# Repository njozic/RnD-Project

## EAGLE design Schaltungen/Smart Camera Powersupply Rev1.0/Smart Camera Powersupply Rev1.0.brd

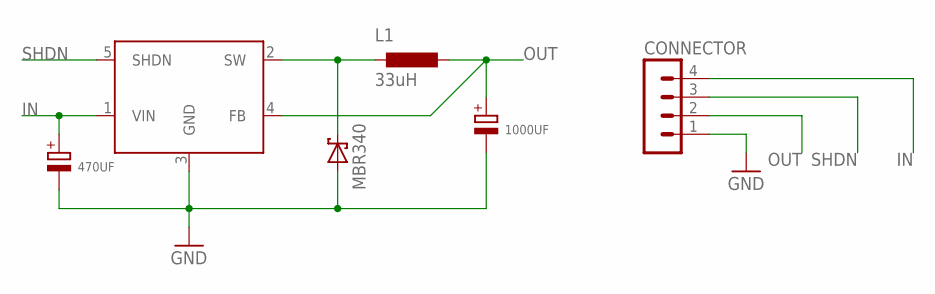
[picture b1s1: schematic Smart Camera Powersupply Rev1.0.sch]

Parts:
C1: 1000UF
C2: 470UF
CONNECTOR: MA04-1
L1: 33uH; L_33UH
U$1: MBR340
U$2: MIC4576

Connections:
GND: C1.P$2, C2.P$2, CONNECTOR.1, U$1.P$2 (C), U$2.3 (GND)
IN: C2.P$1, CONNECTOR.4, U$2.1 (VIN)
unnamed: L1.P$2, U$1.P$1 (A), U$2.2 (SW)
OUT: C1.P$1, CONNECTOR.2, L1.P$1, U$2.4 (FB)
SHDN: CONNECTOR.3, U$2.5 (SHDN)

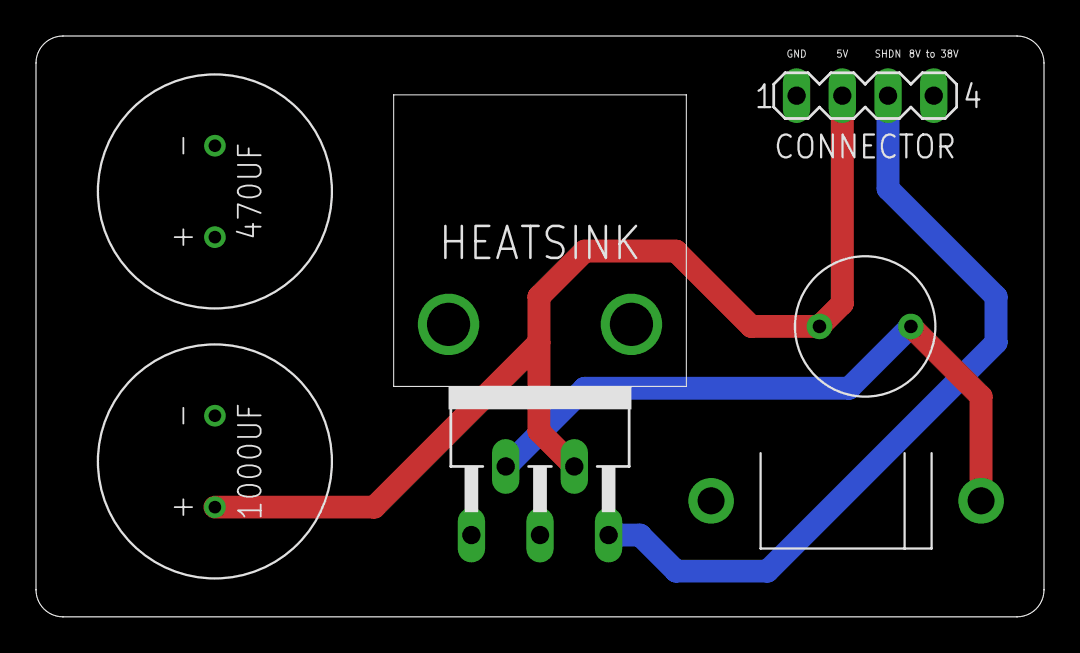
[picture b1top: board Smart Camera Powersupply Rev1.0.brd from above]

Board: 2 copper layers, 56.0 x 32.3 mm, 6 parts (0 on the bottom side), 5 nets.

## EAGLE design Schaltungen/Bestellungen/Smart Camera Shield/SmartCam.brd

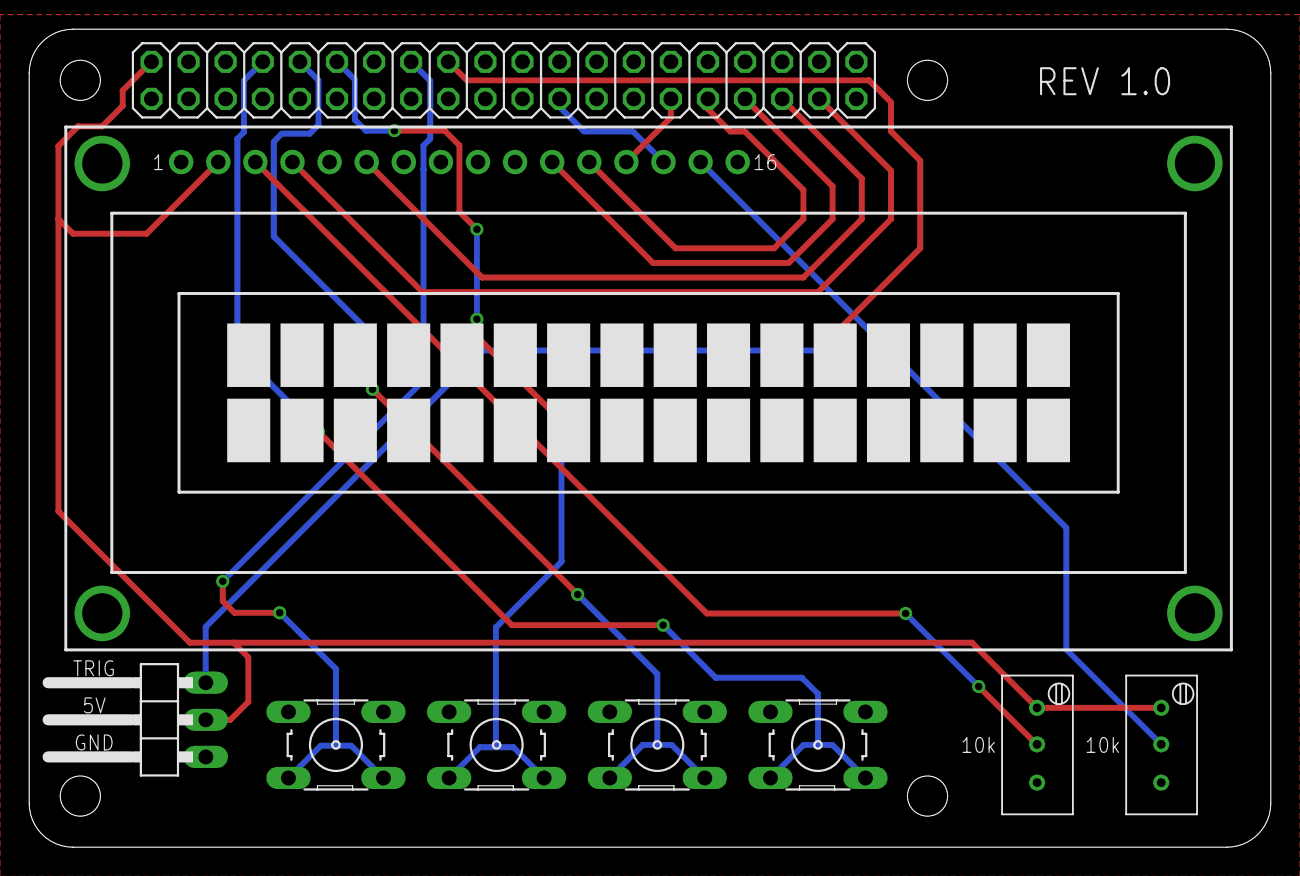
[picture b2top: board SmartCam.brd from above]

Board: 2 copper layers, 85.0 x 56.0 mm, 9 parts (0 on the bottom side), 15 nets.

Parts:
DISP1: LCD_16X2_HD44780
JP1: GPIO; 2X20
JP2: 1X03/90
POT1, POT2: 10k; BOURNS_WEL3296_W_103
S1: ML; B3F-10XX
S2: UR; B3F-10XX
S3: UL; B3F-10XX
S4: MR; B3F-10XX

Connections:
DB4: DISP1.11, JP1.33
DB5: DISP1.12, JP1.31
DB6: DISP1.13, JP1.29
DB7: DISP1.14, JP1.23
E: DISP1.6, JP1.35
GND: DISP1.1, DISP1.5, DISP1.16, JP1.6, JP2.1, POT1.P$3, POT2.P$3, S1.1, S1.2, S2.1, S2.2, S3.1, S3.2, S4.1, S4.2
LED+: DISP1.15, POT2.P$2
ML: JP1.8, S1.3, S1.4
MR: JP1.16, S4.3, S4.4
RS: DISP1.4, JP1.37
TRIG: JP1.18, JP2.3
UL: JP1.12, S3.3, S3.4
UR: JP1.10, S2.3, S2.4
V+: DISP1.2, JP1.2, JP2.2, POT1.P$1, POT2.P$1
VO: DISP1.3, POT1.P$2

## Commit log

2020-07-30 init
    transfer project
